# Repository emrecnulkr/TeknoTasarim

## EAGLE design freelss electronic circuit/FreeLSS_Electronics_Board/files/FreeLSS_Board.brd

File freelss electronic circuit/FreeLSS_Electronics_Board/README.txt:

.:                     :,                                          
,:::::::: ::`      :::                   :::                                          
,:::::::: ::`      :::                   :::                                          
.,,:::,,, ::`.:,   ... .. .:,     .:. ..`... ..`   ..   .:,    .. ::  .::,     .:,`   
   ,::    :::::::  ::, :::::::  `:::::::.,:: :::  ::: .::::::  ::::: ::::::  .::::::  
   ,::    :::::::: ::, :::::::: ::::::::.,:: :::  ::: :::,:::, ::::: ::::::, :::::::: 
   ,::    :::  ::: ::, :::  :::`::.  :::.,::  ::,`::`:::   ::: :::  `::,`   :::   ::: 
   ,::    ::.  ::: ::, ::`  :::.::    ::.,::  :::::: ::::::::: ::`   :::::: ::::::::: 
   ,::    ::.  ::: ::, ::`  :::.::    ::.,::  .::::: ::::::::: ::`    ::::::::::::::: 
   ,::    ::.  ::: ::, ::`  ::: ::: `:::.,::   ::::  :::`  ,,, ::`  .::  :::.::.  ,,, 
   ,::    ::.  ::: ::, ::`  ::: ::::::::.,::   ::::   :::::::` ::`   ::::::: :::::::. 
   ,::    ::.  ::: ::, ::`  :::  :::::::`,::    ::.    :::::`  ::`   ::::::   :::::.  
                                ::,  ,::                               ``             
                                ::::::::                                              
                                 ::::::                                               
                                  `,,`

http://www.thingiverse.com/thing:1298438
FreeLSS Electronics Board by C_D is licensed under the Creative Commons - Attribution - Non-Commercial license.
http://creativecommons.org/licenses/by-nc/3.0/

# Summary

This is a small Raspberry Pi 'shield' for controlling a FreeLSS based 3D scanner.

The board measures just 42x52mm, and mounts directly on the Raspberry Pi GPIO port. It has an on board buck converter module which powers the stepper driver (Pololu-style DRV8825 or DRV8832) and also the Rasppberry Pi, so all you need is a single 12-24V plug pack.

-----------------------------------------

I have had enough interest in the PCB's that I have ordered a second batch. Send me a message if you are interested in getting hold of one!

-----------------------------------------

Assembly is pretty straight forward, all components are marked on the board. The only catch is the two MosFETs, check the pinout of the part you are using and make sure you put it in the right way round, the VN10LP for example has the pins the other way round to the outline marked on the board.

Make sure you adjust your DC-DC converter before attaching the board to the Raspberry Pi, you want your 5V output set at 4.9-5.1V

NOTE:
It has been brought to my attention that using an A4988 stepper driver module can be unreliable when using 5V supply and 3V3 logic signals. The minimum logic high voltage is 0.7*VDD or 3.5V, so 3V3 logic may not work on some boards. I have an A4988 driver on my board at home and it does work, however I cannot guarantee it will work in all cases.

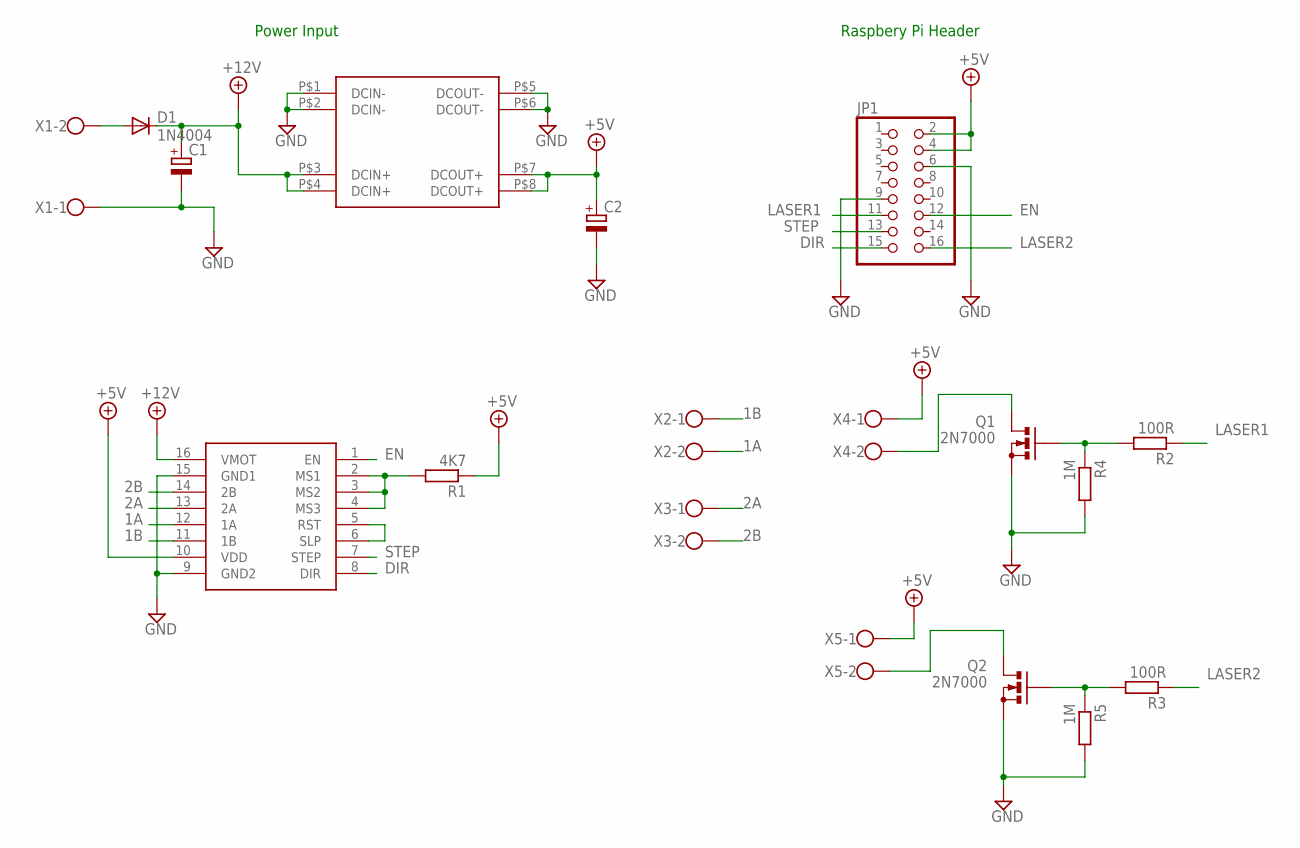
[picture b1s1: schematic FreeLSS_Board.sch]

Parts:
C1, C2: CPOL-EUE2.5-5; E2,5-5
D1: 1N4004; DO35-7
JP1: PINHD-2X8; 2X08
Q1, Q2: 2N7000; SOT54E
R1: 4K7; 0204/7
R2, R3: 100R; 0204/7
R4, R5: 1M; 0204/7
U$1: DC-DC_MODULE_MP1584
U$2: POLOLU_STEPSTICK
X1, X2, X3, X4, X5: W237-102

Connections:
1A: U$2.12 (1A), X2.2
1B: U$2.11 (1B), X2.1
2A: U$2.13 (2A), X3.1
2B: U$2.14 (2B), X3.2
+5V: C2.+, JP1.2, JP1.4, R1.1, U$1.P$7 (DCOUT+), U$1.P$8 (DCOUT+), U$2.10 (VDD), X4.1, X5.1
+12V: C1.+, D1.C, U$1.P$3 (DCIN+), U$1.P$4 (DCIN+), U$2.16 (VMOT)
DIR: JP1.15, U$2.8 (DIR)
EN: JP1.12, U$2.1 (EN)
GND: C1.-, C2.-, JP1.6, JP1.9, Q1.S, Q2.S, R4.2, R5.2, U$1.P$1 (DCIN-), U$1.P$2 (DCIN-), U$1.P$5 (DCOUT-), U$1.P$6 (DCOUT-), U$2.9 (GND2), U$2.15 (GND1), X1.1
LASER1: JP1.11, R2.1
LASER2: JP1.16, R3.1
unnamed: D1.A, X1.2
unnamed: Q1.G, R2.2, R4.1
unnamed: Q2.G, R3.2, R5.1
unnamed: R1.2, U$2.2 (MS1), U$2.3 (MS2), U$2.4 (MS3)
unnamed: Q1.D, X4.2
unnamed: U$2.5 (RST), U$2.6 (SLP)
unnamed: Q2.D, X5.2
STEP: JP1.13, U$2.7 (STEP)

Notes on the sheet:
Raspbery Pi Header
Power Input

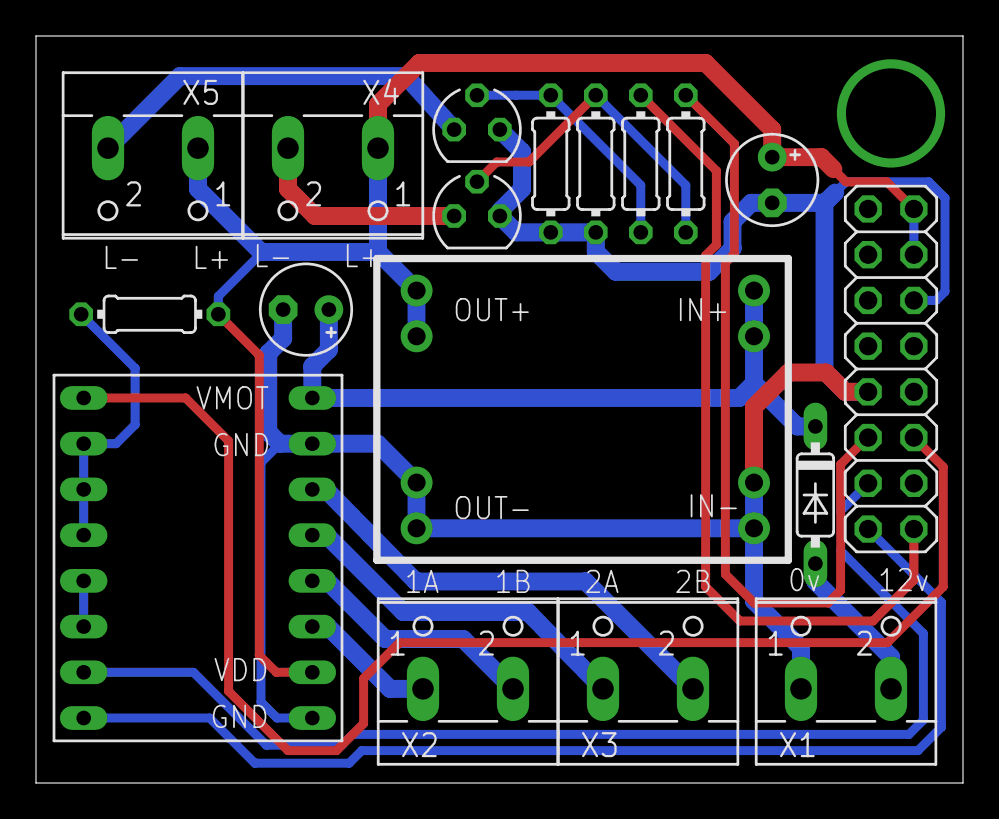
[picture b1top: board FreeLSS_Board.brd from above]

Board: 2 copper layers, 51.5 x 41.5 mm, 18 parts (0 on the bottom side), 19 nets.

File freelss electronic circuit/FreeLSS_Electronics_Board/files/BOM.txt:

1 x Pololu compatible stepper driver
1 x MP1584 DCDC Module (eg. http://www.ebay.com/itm/Mini-3A-DC-DC-Adjustable-Step-down-C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 )
2 x 100R resistor
2 x 1M resistor
1 x 4K7 resistor
2 x 47uF 35V electrolytic capacitor
1 x 1N4004 diode (or similar)
2 x VN10LP (or 2N7000 or BS170)
5 x 5.0mm pitch PCB terminal block 2 way
1 x 2.54 pitch female header 2 x 8 way

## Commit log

2017-07-11 Arastirmalar
